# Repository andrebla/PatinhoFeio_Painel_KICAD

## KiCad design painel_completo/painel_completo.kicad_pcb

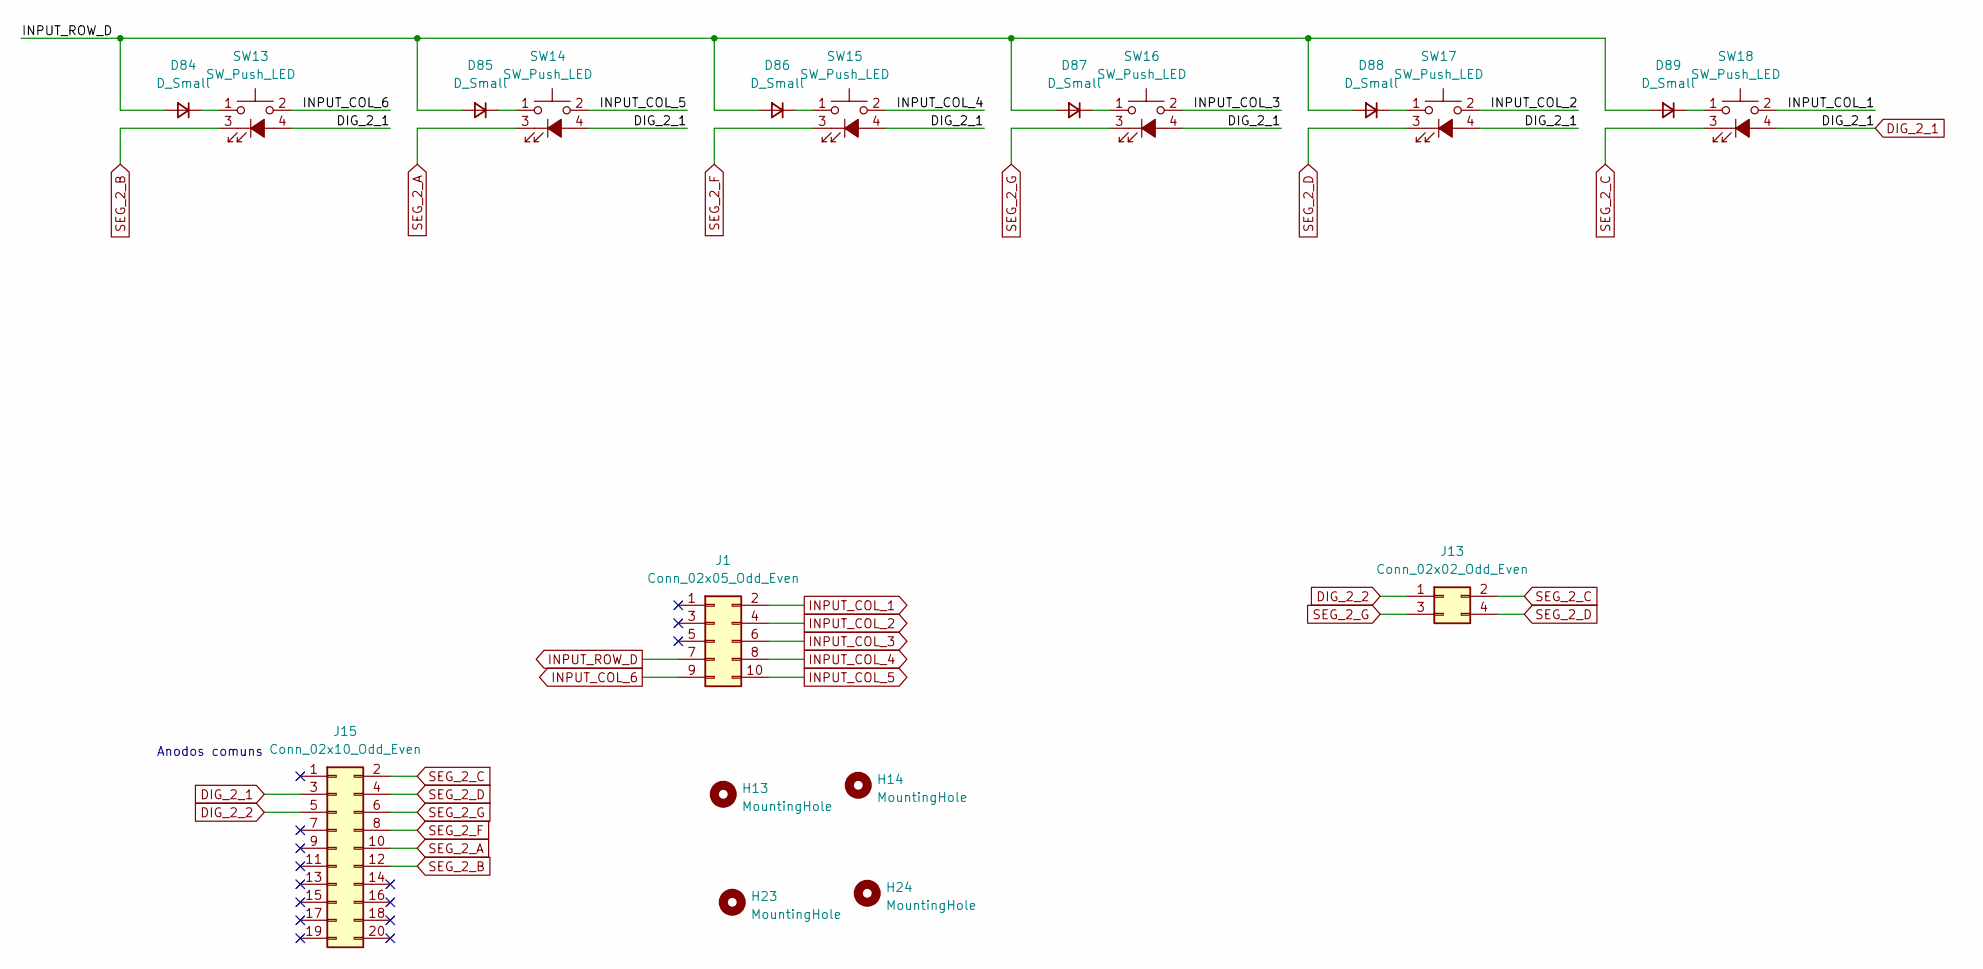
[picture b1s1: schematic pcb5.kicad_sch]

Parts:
D84, D85, D86, D87, D88, D89: D_Small; D_DO-35_SOD27_P7.62mm_Horizontal
H13, H14, H23, H24: MountingHole; MountingHole_3.2mm_M3
J1: Conn_02x05_Odd_Even; PinHeader_2x05_P2.54mm_Vertical
J13: Conn_02x02_Odd_Even; PinHeader_2x02_P2.54mm_Vertical
J15: Conn_02x10_Odd_Even; PinHeader_2x10_P2.54mm_Vertical
SW13, SW14, SW15, SW16, SW17, SW18: SW_Push_LED; R16-503

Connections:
DIG_2_1: J15.3, SW13.4 (A), SW14.4 (A), SW15.4 (A), SW16.4 (A), SW17.4 (A), SW18.4 (A); also elsewhere on the board
DIG_2_2: J13.1, J15.5; also elsewhere on the board
GPIO9: D84.2 (A), D85.2 (A), D86.2 (A), D87.2 (A), D88.2 (A), D89.2 (A), J1.7; also elsewhere on the board
GPIO10: J1.2, SW18.2; also elsewhere on the board
GPIO11: J1.4, SW17.2; also elsewhere on the board
GPIO12: J1.6, SW16.2; also elsewhere on the board
GPIO13: J1.8, SW15.2; also elsewhere on the board
GPIO14: J1.10, SW14.2; also elsewhere on the board
GPIO15: J1.9, SW13.2; also elsewhere on the board
unnamed: D84.1 (K), SW13.1
unnamed: D85.1 (K), SW14.1
unnamed: D86.1 (K), SW15.1
unnamed: D87.1 (K), SW16.1
unnamed: D88.1 (K), SW17.1
unnamed: D89.1 (K), SW18.1
SEG_2_A: J15.10, SW14.3 (K); also elsewhere on the board
SEG_2_B: J15.12, SW13.3 (K); also elsewhere on the board
SEG_2_C: J13.2, J15.2, SW18.3 (K); also elsewhere on the board
SEG_2_D: J13.4, J15.4, SW17.3 (K); also elsewhere on the board
SEG_2_F: J15.8, SW15.3 (K); also elsewhere on the board
SEG_2_G: J13.3, J15.6, SW16.3 (K); also elsewhere on the board

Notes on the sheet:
Anodos comuns

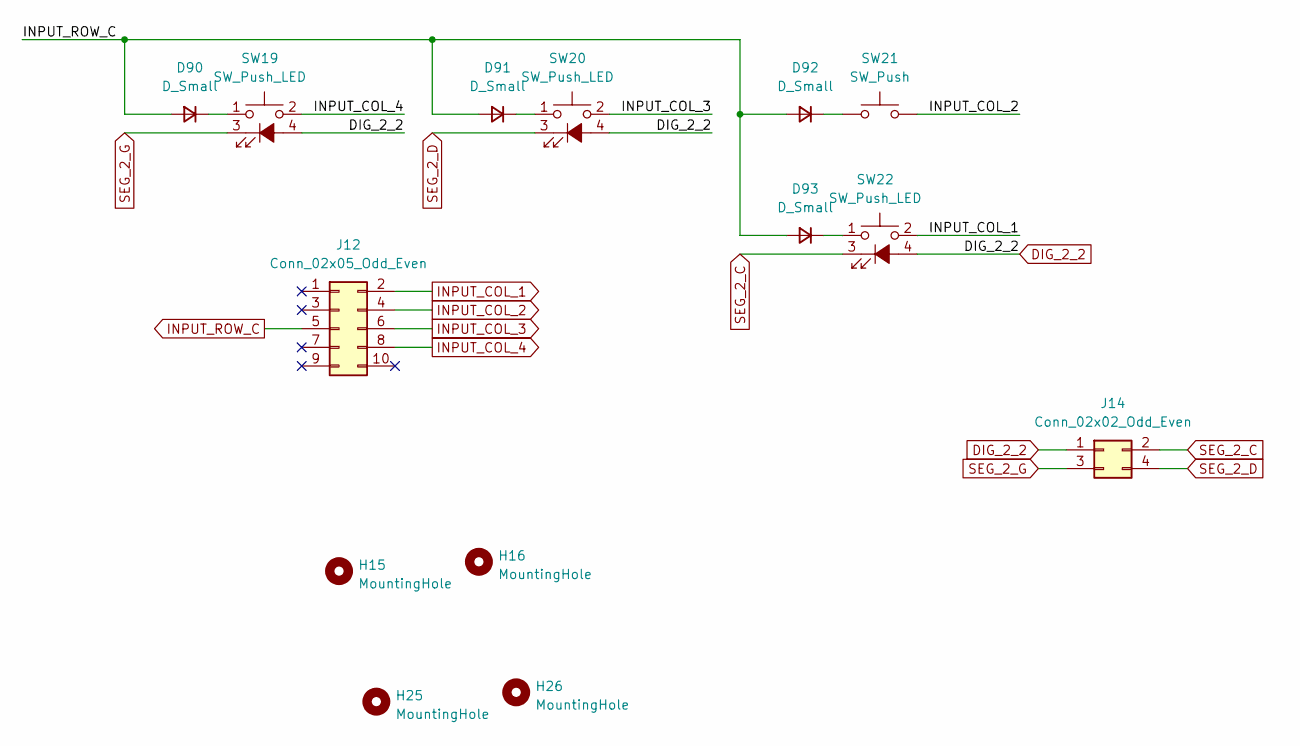
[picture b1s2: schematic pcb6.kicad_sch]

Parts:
D90, D91, D92, D93: D_Small; D_DO-35_SOD27_P7.62mm_Horizontal
H15, H16, H25, H26: MountingHole; MountingHole_3.2mm_M3
J12: Conn_02x05_Odd_Even; PinHeader_2x05_P2.54mm_Vertical
J14: Conn_02x02_Odd_Even; PinHeader_2x02_P2.54mm_Vertical
SW19, SW20, SW22: SW_Push_LED; R16-503
SW21: SW_Push; PinHeader_1x02_P2.54mm_Vertical

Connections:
DIG_2_2: J14.1, SW19.4 (A), SW20.4 (A), SW22.4 (A); also elsewhere on the board
GPIO8: D90.2 (A), D91.2 (A), D92.2 (A), D93.2 (A), J12.5; also elsewhere on the board
GPIO10: J12.2, SW22.2; also elsewhere on the board
GPIO11: J12.4, SW21.2; also elsewhere on the board
GPIO12: J12.6, SW20.2; also elsewhere on the board
GPIO13: J12.8, SW19.2; also elsewhere on the board
unnamed: D90.1 (K), SW19.1
unnamed: D91.1 (K), SW20.1
unnamed: D92.1 (K), SW21.1
unnamed: D93.1 (K), SW22.1
SEG_2_C: J14.2, SW22.3 (K); also elsewhere on the board
SEG_2_D: J14.4, SW20.3 (K); also elsewhere on the board
SEG_2_G: J14.3, SW19.3 (K); also elsewhere on the board

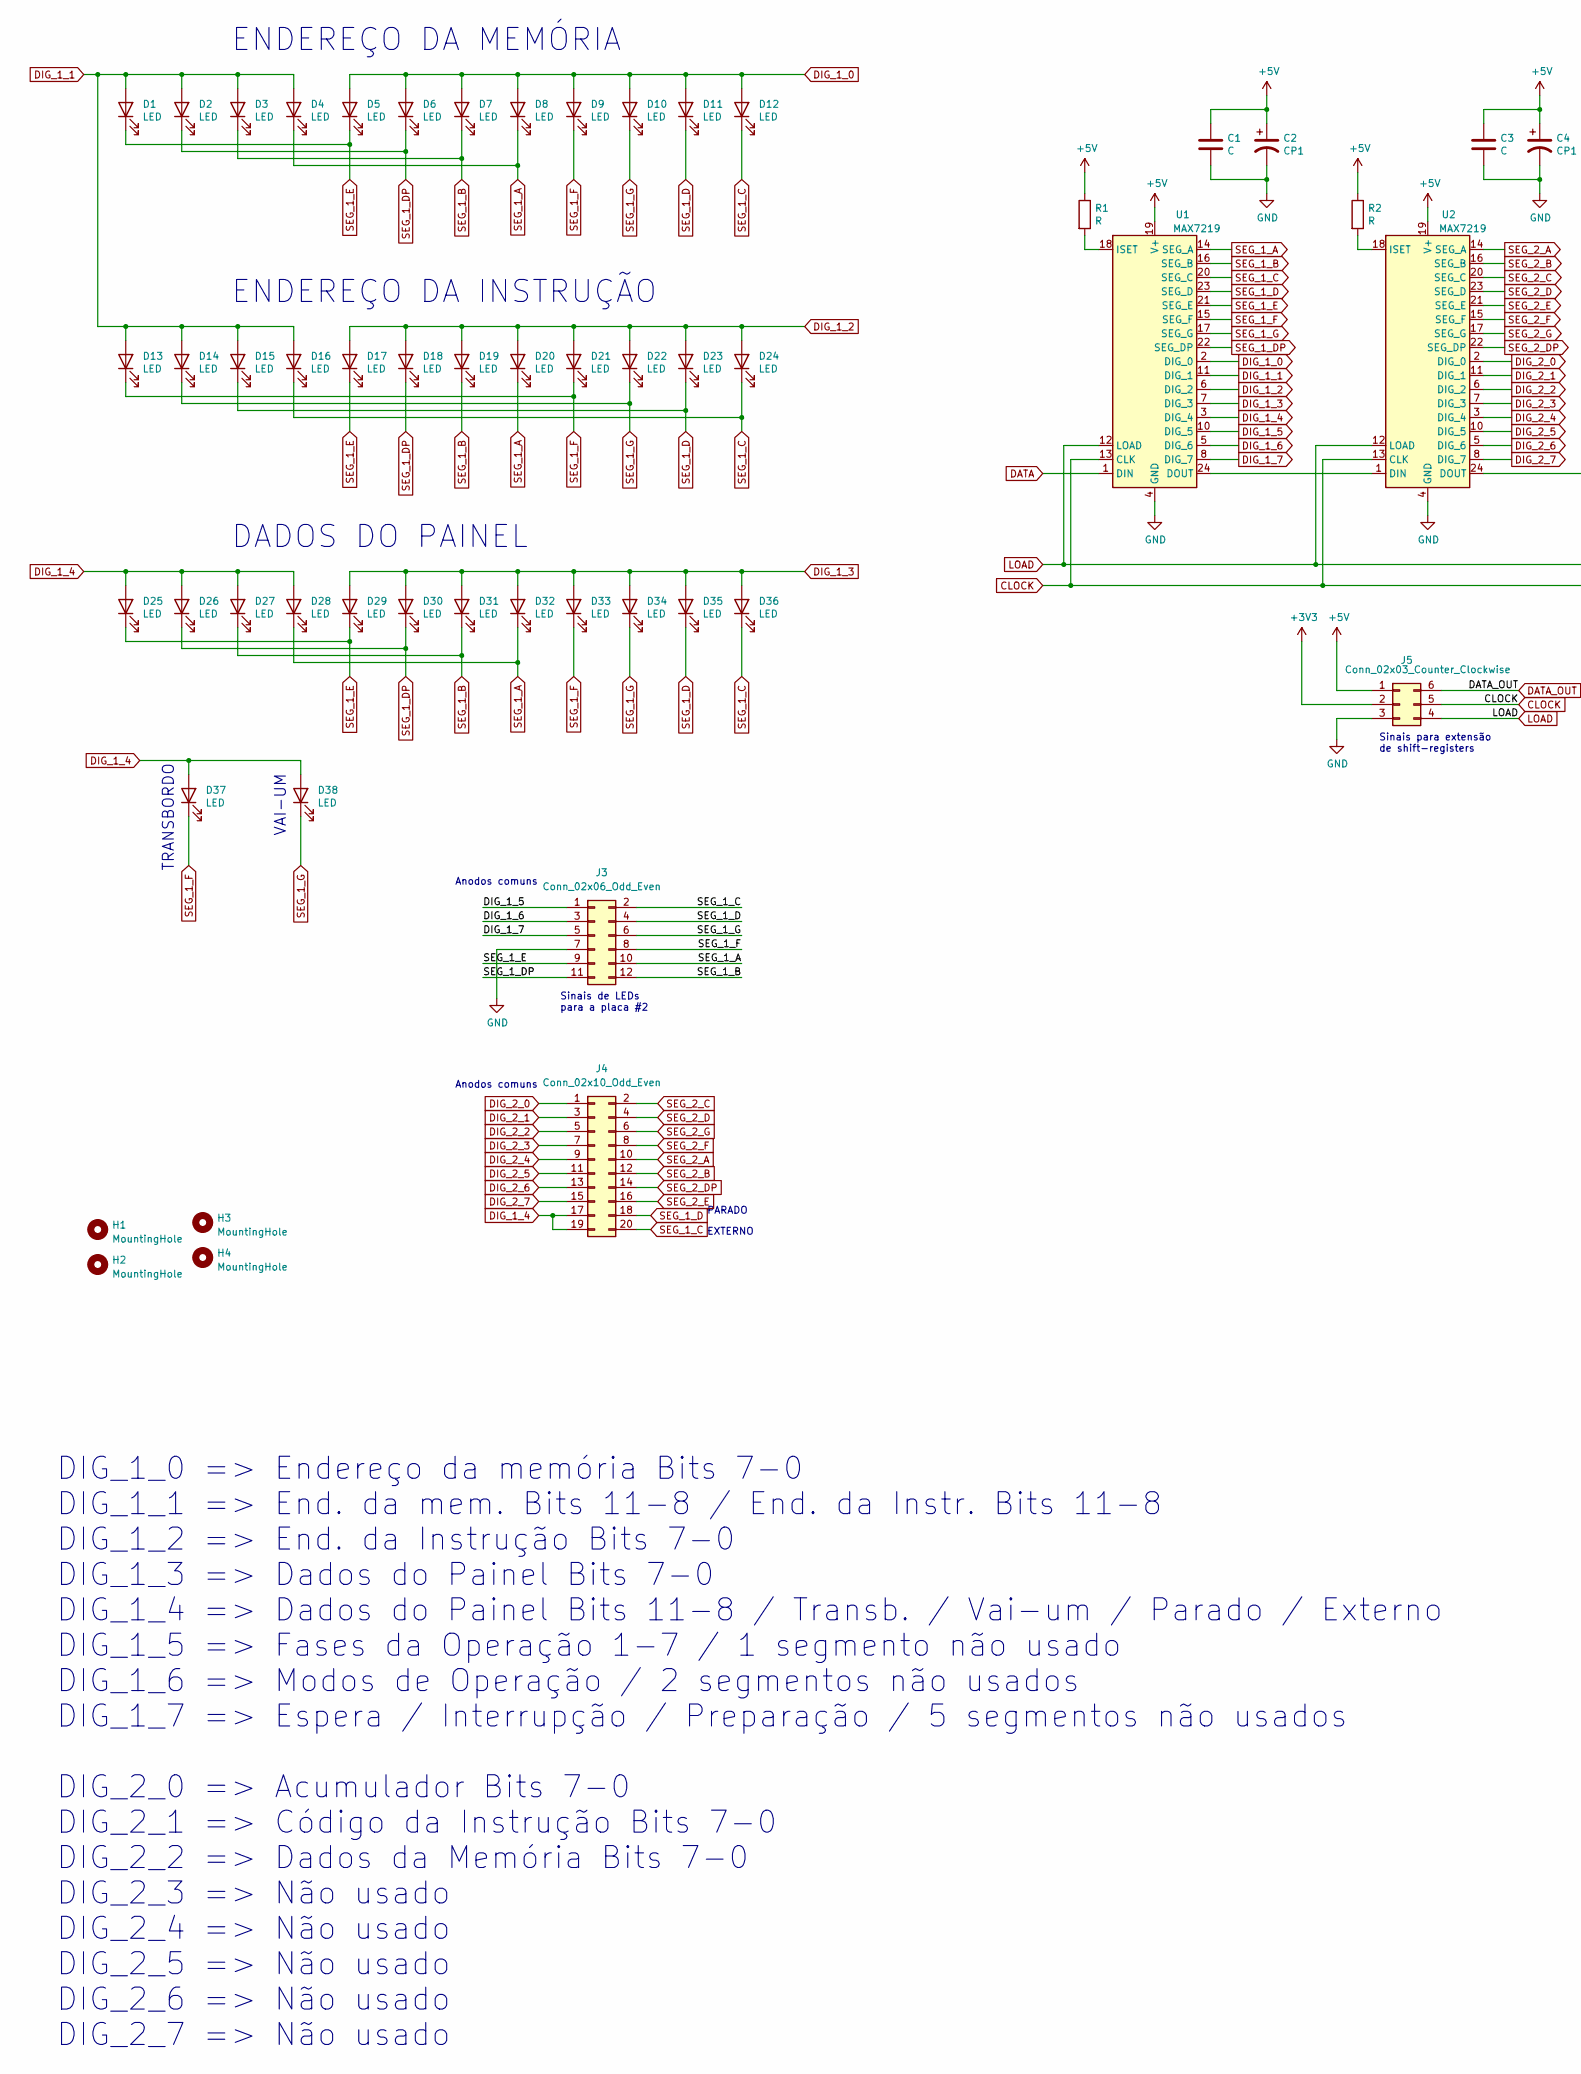
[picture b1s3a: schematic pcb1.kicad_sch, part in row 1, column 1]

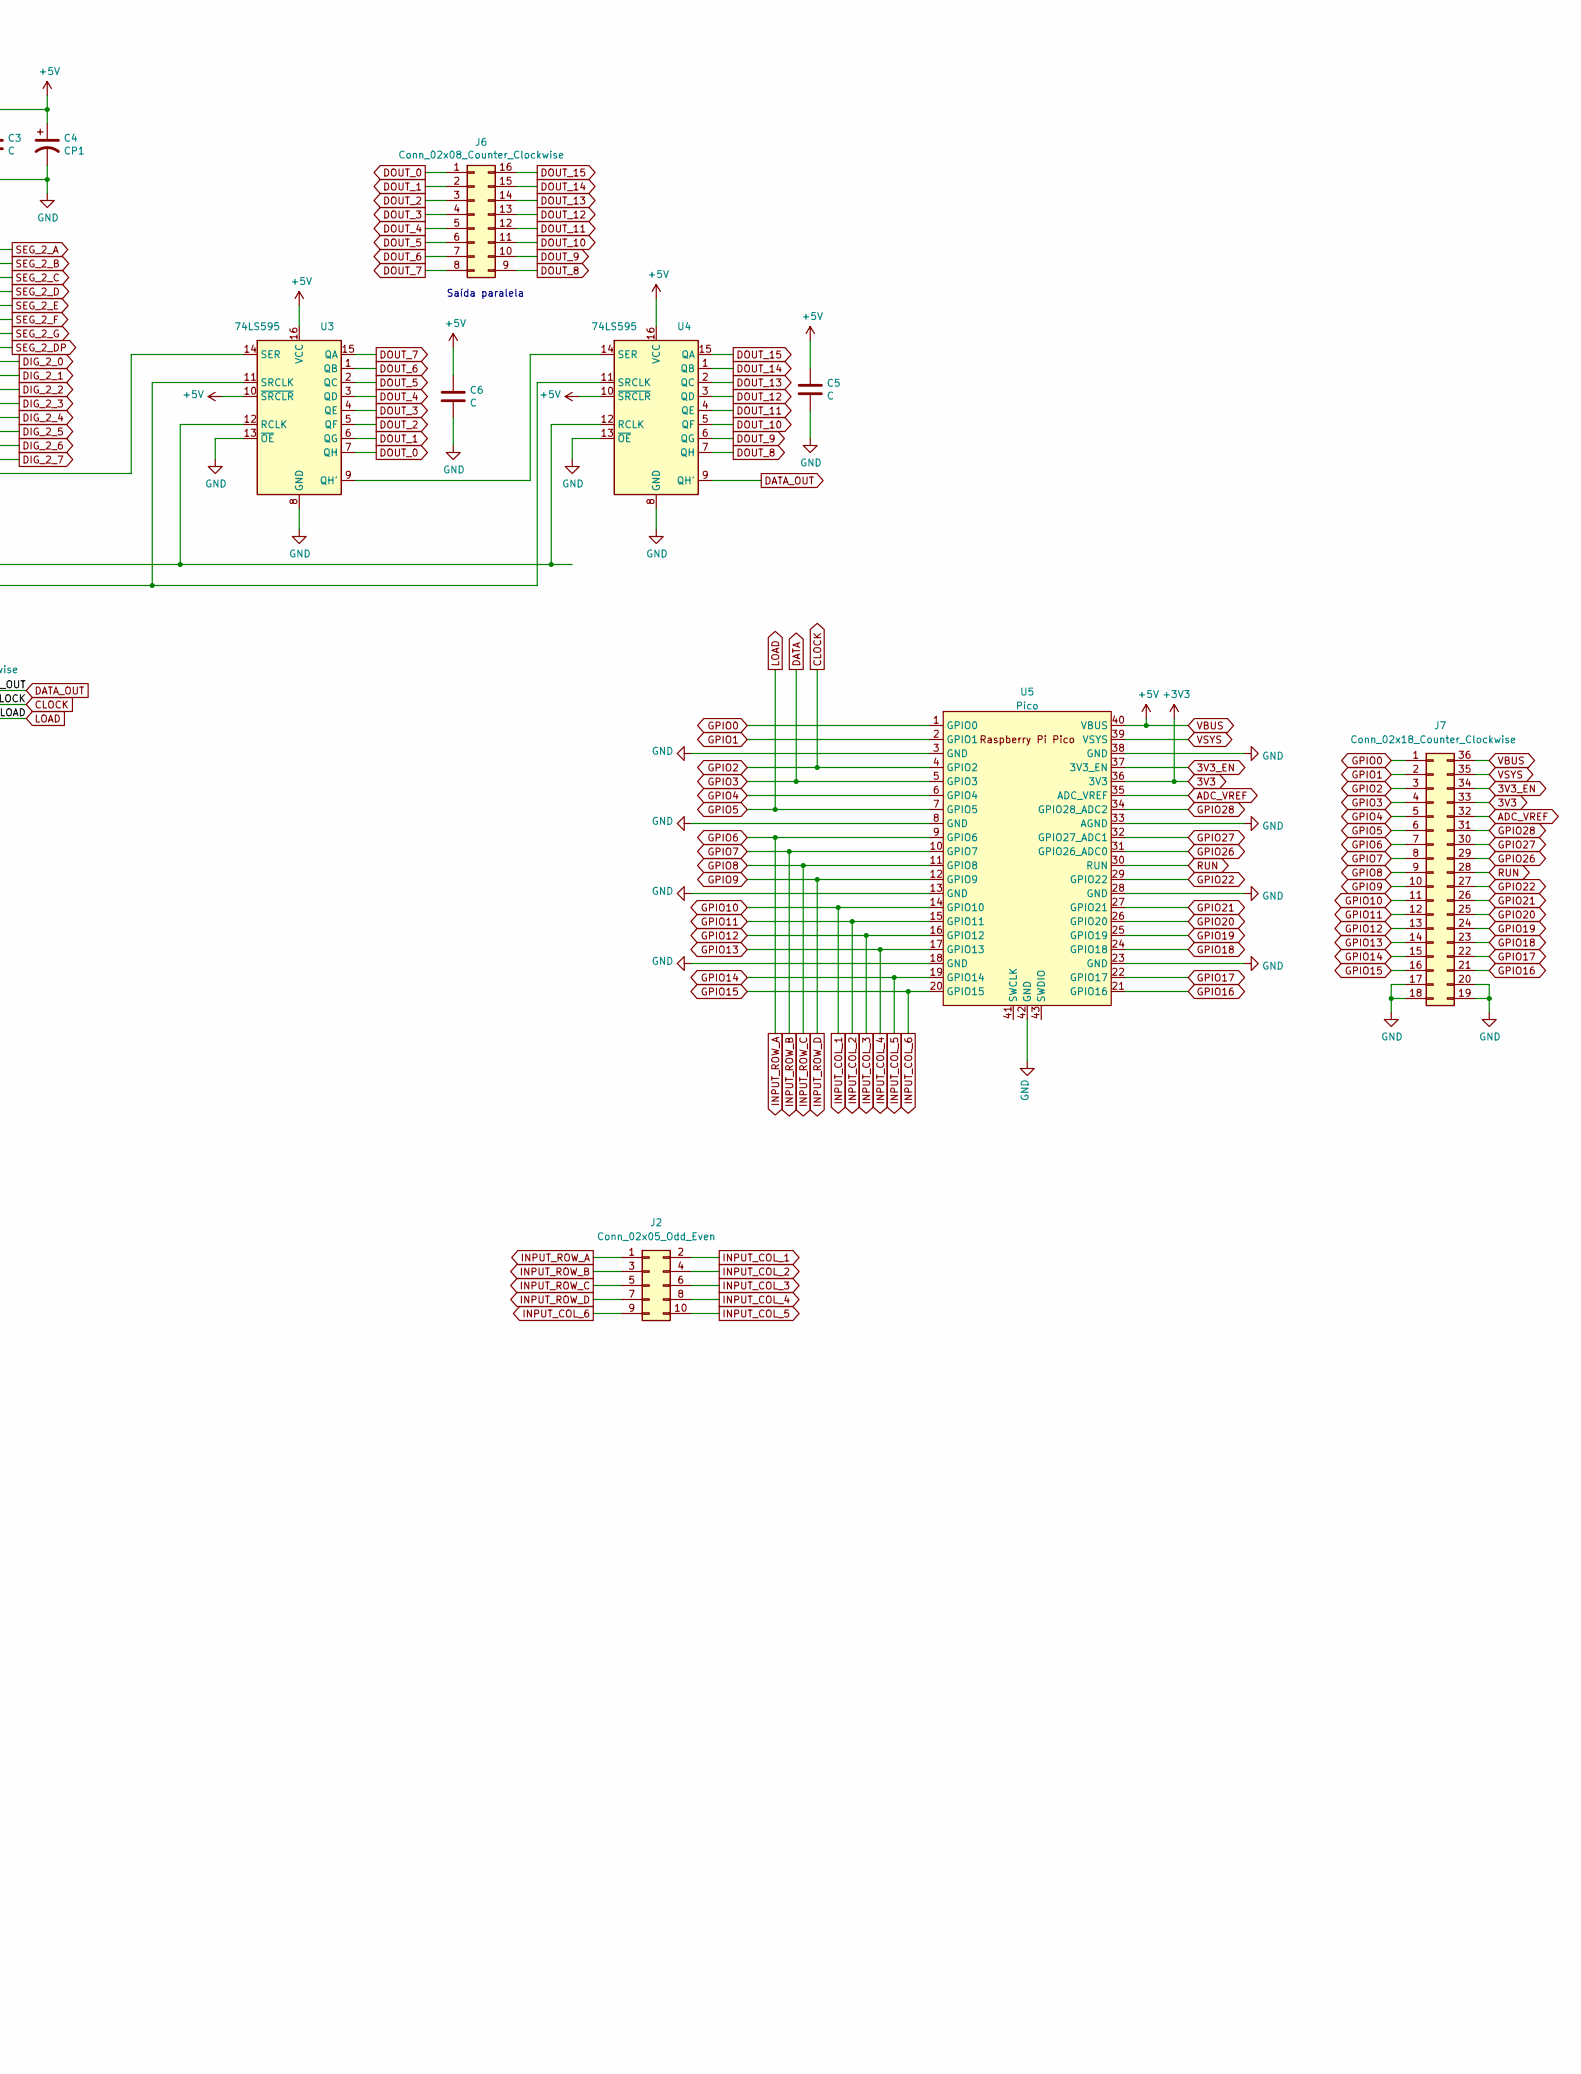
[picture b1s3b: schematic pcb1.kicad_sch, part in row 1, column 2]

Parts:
C1, C3, C5, C6: C; C_Disc_D5.0mm_W2.5mm_P2.50mm
C2, C4: CP1; CP_Radial_D4.0mm_P2.00mm
D1, D2, D3, D4, D5, D6, D7, D8, D9, D10, D11, D12, D13, D14, D15, D16, D17, D18, D19, D20, D21, D22, D23, D24, D25, D26, D27, D28, D29, D30, D31, D32, D33, D34, D35, D36, D37, D38: LED; LED_D3.0mm
H1, H2, H3, H4: MountingHole; MountingHole_3.2mm_M3
J2: Conn_02x05_Odd_Even; PinHeader_2x05_P2.54mm_Vertical
J3: Conn_02x06_Odd_Even; PinHeader_2x06_P2.54mm_Vertical
J4: Conn_02x10_Odd_Even; PinHeader_2x10_P2.54mm_Vertical
J5: Conn_02x03_Counter_Clockwise; PinHeader_2x03_P2.54mm_Vertical
J6: Conn_02x08_Counter_Clockwise; PinHeader_2x08_P2.54mm_Vertical
J7: Conn_02x18_Counter_Clockwise; PinHeader_2x18_P2.54mm_Vertical
R1, R2: R; R_Axial_DIN0207_L6.3mm_D2.5mm_P10.16mm_Horizontal
U1, U2: MAX7219; DIP-24_W7.62mm_Socket_LongPads
U3, U4: 74LS595; DIP-16_W7.62mm_LongPads
U5: Pico; RPi_Pico_SMD_TH

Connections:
3V3: J5.2, J7.33, U5.36 (3V3)
3V3_EN: J7.34, U5.37 (3V3_EN)
ADC_VREF: J7.32, U5.35 (ADC_VREF)
CLOCK: J5.5, J7.3, U1.13 (CLK), U2.13 (CLK), U3.11 (SRCLK), U4.11 (SRCLK), U5.4 (GPIO2)
DATA: J7.4, U1.1 (DIN), U5.5 (GPIO3)
DATA_OUT: J5.6, U4.9 (QH')
DIG_1_0: D5.2 (A), D6.2 (A), D7.2 (A), D8.2 (A), D9.2 (A), D10.2 (A), D11.2 (A), D12.2 (A), U1.2 (DIG_0)
DIG_1_1: D1.2 (A), D2.2 (A), D3.2 (A), D4.2 (A), D13.2 (A), D14.2 (A), D15.2 (A), D16.2 (A), U1.11 (DIG_1)
DIG_1_2: D17.2 (A), D18.2 (A), D19.2 (A), D20.2 (A), D21.2 (A), D22.2 (A), D23.2 (A), D24.2 (A), U1.6 (DIG_2)
DIG_1_3: D29.2 (A), D30.2 (A), D31.2 (A), D32.2 (A), D33.2 (A), D34.2 (A), D35.2 (A), D36.2 (A), U1.7 (DIG_3)
DIG_1_4: D25.2 (A), D26.2 (A), D27.2 (A), D28.2 (A), D37.2 (A), D38.2 (A), J4.17, J4.19, U1.3 (DIG_4); also elsewhere on the board
DIG_1_5: J3.1, U1.10 (DIG_5)
DIG_1_6: J3.3, U1.5 (DIG_6)
DIG_1_7: J3.5, U1.8 (DIG_7)
DIG_2_0: J4.1, U2.2 (DIG_0); also elsewhere on the board
DIG_2_1: J4.3, U2.11 (DIG_1); also elsewhere on the board
DIG_2_2: J4.5, U2.6 (DIG_2); also elsewhere on the board
DIG_2_3: J4.7, U2.7 (DIG_3); also elsewhere on the board
DIG_2_4: J4.9, U2.3 (DIG_4); also elsewhere on the board
DIG_2_5: J4.11, U2.10 (DIG_5); also elsewhere on the board
DIG_2_6: J4.13, U2.5 (DIG_6); also elsewhere on the board
DIG_2_7: J4.15, U2.8 (DIG_7); also elsewhere on the board
DOUT_0: J6.1, U3.7 (QH)
DOUT_1: J6.2, U3.6 (QG)
DOUT_2: J6.3, U3.5 (QF)
DOUT_3: J6.4, U3.4 (QE)
DOUT_4: J6.5, U3.3 (QD)
DOUT_5: J6.6, U3.2 (QC)
DOUT_6: J6.7, U3.1 (QB)
DOUT_7: J6.8, U3.15 (QA)
DOUT_8: J6.9, U4.7 (QH)
DOUT_9: J6.10, U4.6 (QG)
DOUT_10: J6.11, U4.5 (QF)
DOUT_11: J6.12, U4.4 (QE)
DOUT_12: J6.13, U4.3 (QD)
DOUT_13: J6.14, U4.2 (QC)
DOUT_14: J6.15, U4.1 (QB)
DOUT_15: J6.16, U4.15 (QA)
GND: C1.2, C2.2, C3.2, C4.2, C5.2, C6.2, J3.7, J5.3, J7.17, J7.18, J7.19, J7.20, U1.4 (GND), U1.9 (GND), U2.4 (GND), U2.9 (GND), U3.8 (GND), U3.13 (~OE), U4.8 (GND), U4.13 (~OE), U5.3 (GND), U5.8 (GND), U5.13 (GND), U5.18 (GND), U5.23 (GND), U5.28 (GND), U5.33 (AGND), U5.38 (GND), U5.42 (GND); also elsewhere on the board
GPIO0: J7.1, U5.1 (GPIO0)
GPIO1: J7.2, U5.2 (GPIO1)
GPIO4: J7.5, U5.6 (GPIO4)
GPIO5: J5.4, J7.6, U1.12 (LOAD), U2.12 (LOAD), U3.12 (RCLK), U4.12 (RCLK), U5.7 (GPIO5)
GPIO6: J2.1, J7.7, U5.9 (GPIO6); also elsewhere on the board
GPIO7: J2.3, J7.8, U5.10 (GPIO7); also elsewhere on the board
GPIO8: J2.5, J7.9, U5.11 (GPIO8); also elsewhere on the board
GPIO9: J2.7, J7.10, U5.12 (GPIO9); also elsewhere on the board
GPIO10: J2.2, J7.11, U5.14 (GPIO10); also elsewhere on the board
GPIO11: J2.4, J7.12, U5.15 (GPIO11); also elsewhere on the board
GPIO12: J2.6, J7.13, U5.16 (GPIO12); also elsewhere on the board
GPIO13: J2.8, J7.14, U5.17 (GPIO13); also elsewhere on the board
GPIO14: J2.10, J7.15, U5.19 (GPIO14); also elsewhere on the board
GPIO15: J2.9, J7.16, U5.20 (GPIO15); also elsewhere on the board
GPIO16: J7.21, U5.21 (GPIO16)
GPIO17: J7.22, U5.22 (GPIO17)
GPIO18: J7.23, U5.24 (GPIO18)
GPIO19: J7.24, U5.25 (GPIO19)
GPIO20: J7.25, U5.26 (GPIO20)
GPIO21: J7.26, U5.27 (GPIO21)
GPIO22: J7.27, U5.29 (GPIO22)
GPIO26: J7.29, U5.31 (GPIO26_ADC0)
GPIO27: J7.30, U5.32 (GPIO27_ADC1)
GPIO28: J7.31, U5.34 (GPIO28_ADC2)
unnamed: R1.2, U1.18 (ISET)
unnamed: R2.2, U2.18 (ISET)
unnamed: U1.24 (DOUT), U2.1 (DIN)
unnamed: U2.24 (DOUT), U3.14 (SER)
unnamed: U3.9 (QH'), U4.14 (SER)
RUN: J7.28, U5.30 (RUN)
SEG_1_A: D4.1 (K), D8.1 (K), D20.1 (K), D28.1 (K), D32.1 (K), J3.10, U1.14 (SEG_A)
SEG_1_B: D3.1 (K), D7.1 (K), D19.1 (K), D27.1 (K), D31.1 (K), J3.12, U1.16 (SEG_B)
SEG_1_C: D12.1 (K), D16.1 (K), D24.1 (K), D36.1 (K), J3.2, J4.20, U1.20 (SEG_C); also elsewhere on the board
SEG_1_D: D11.1 (K), D15.1 (K), D23.1 (K), D35.1 (K), J3.4, J4.18, U1.23 (SEG_D); also elsewhere on the board
SEG_1_DP: D2.1 (K), D6.1 (K), D18.1 (K), D26.1 (K), D30.1 (K), J3.11, U1.22 (SEG_DP)
SEG_1_E: D1.1 (K), D5.1 (K), D17.1 (K), D25.1 (K), D29.1 (K), J3.9, U1.21 (SEG_E)
SEG_1_F: D9.1 (K), D13.1 (K), D21.1 (K), D33.1 (K), D37.1 (K), J3.8, U1.15 (SEG_F)
SEG_1_G: D10.1 (K), D14.1 (K), D22.1 (K), D34.1 (K), D38.1 (K), J3.6, U1.17 (SEG_G)
SEG_2_A: J4.10, U2.14 (SEG_A); also elsewhere on the board
SEG_2_B: J4.12, U2.16 (SEG_B); also elsewhere on the board
SEG_2_C: J4.2, U2.20 (SEG_C); also elsewhere on the board
SEG_2_D: J4.4, U2.23 (SEG_D); also elsewhere on the board
SEG_2_DP: J4.14, U2.22 (SEG_DP); also elsewhere on the board
SEG_2_E: J4.16, U2.21 (SEG_E); also elsewhere on the board
SEG_2_F: J4.8, U2.15 (SEG_F); also elsewhere on the board
SEG_2_G: J4.6, U2.17 (SEG_G); also elsewhere on the board
VBUS: C1.1, C2.1, C3.1, C4.1, C5.1, C6.1, J5.1, J7.36, R1.1, R2.1, U1.19 (V+), U2.19 (V+), U3.10 (~SRCLR), U3.16 (VCC), U4.10 (~SRCLR), U4.16 (VCC), U5.40 (VBUS)
VSYS: J7.35, U5.39 (VSYS)

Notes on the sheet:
VAI-UM
ENDEREÇO DA INSTRUÇÃO
EXTERNO
PARADO
Sinais para extensão de shift-registers
Sinais de LEDs para a placa #2
Saída paralela
Anodos comuns
DADOS DO PAINEL
ENDEREÇO DA MEMÓRIA
TRANSBORDO
DIG_1_0 => Endereço da memória Bits 7-0 DIG_1_1 => End. da mem. Bits 11-8 / End. da Instr. Bits 11-8 DIG_1_2 => End. da Instrução Bits 7-0 DIG_1_3 => Dados do Painel Bits 7-0 DIG_1_4 => Dados do Painel Bits 11-8 / Transb. / Vai-um / Parado / Externo DIG_1_5 => Fases da Operação 1-7 / 1 segmento não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

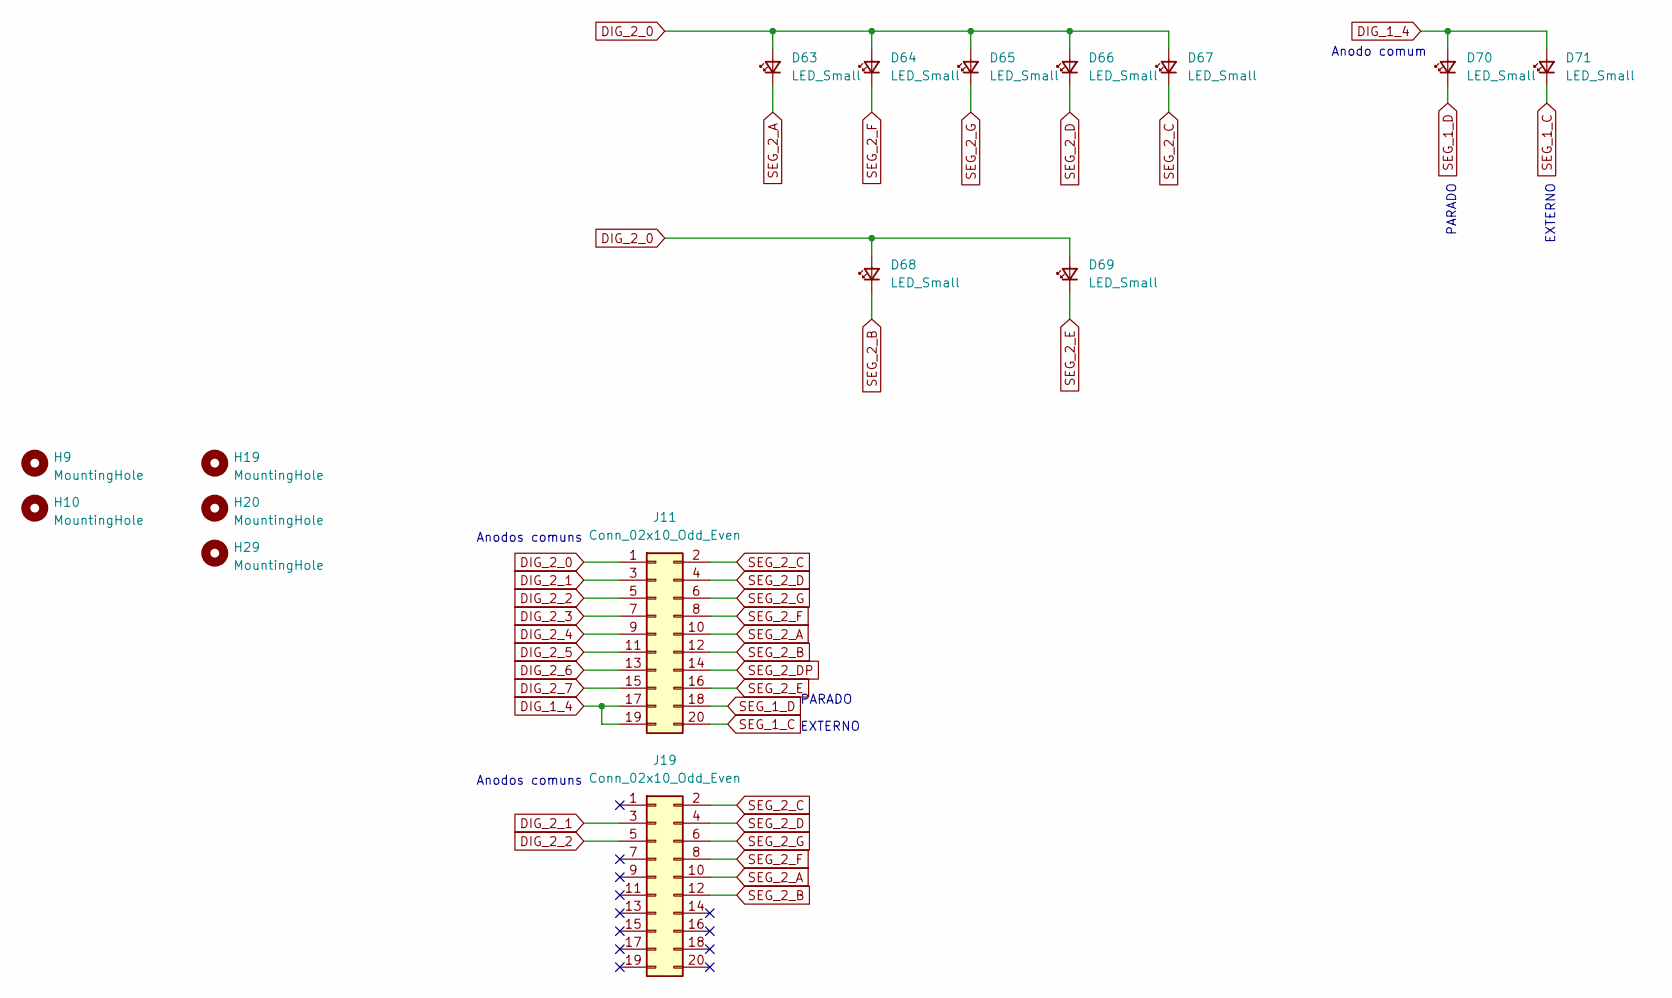
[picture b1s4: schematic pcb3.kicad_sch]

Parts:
D63, D64, D65, D66, D67, D68, D69, D70, D71: LED_Small; LED_D5.0mm
H9, H10, H19, H20, H29: MountingHole; MountingHole_3.2mm_M3
J11, J19: Conn_02x10_Odd_Even; PinHeader_2x10_P2.54mm_Vertical

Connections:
DIG_1_4: D70.2 (A), D71.2 (A), J11.17, J11.19; also elsewhere on the board
DIG_2_0: D63.2 (A), D64.2 (A), D65.2 (A), D66.2 (A), D67.2 (A), D68.2 (A), D69.2 (A), J11.1; also elsewhere on the board
DIG_2_1: J11.3, J19.3; also elsewhere on the board
DIG_2_2: J11.5, J19.5; also elsewhere on the board
DIG_2_3: J11.7; also elsewhere on the board
DIG_2_4: J11.9; also elsewhere on the board
DIG_2_5: J11.11; also elsewhere on the board
DIG_2_6: J11.13; also elsewhere on the board
DIG_2_7: J11.15; also elsewhere on the board
SEG_1_C: D71.1 (K), J11.20; also elsewhere on the board
SEG_1_D: D70.1 (K), J11.18; also elsewhere on the board
SEG_2_A: D63.1 (K), J11.10, J19.10; also elsewhere on the board
SEG_2_B: D68.1 (K), J11.12, J19.12; also elsewhere on the board
SEG_2_C: D67.1 (K), J11.2, J19.2; also elsewhere on the board
SEG_2_D: D66.1 (K), J11.4, J19.4; also elsewhere on the board
SEG_2_DP: J11.14; also elsewhere on the board
SEG_2_E: D69.1 (K), J11.16; also elsewhere on the board
SEG_2_F: D64.1 (K), J11.8, J19.8; also elsewhere on the board
SEG_2_G: D65.1 (K), J11.6, J19.6; also elsewhere on the board

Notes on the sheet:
EXTERNO
PARADO
Anodo comum
Anodos comuns

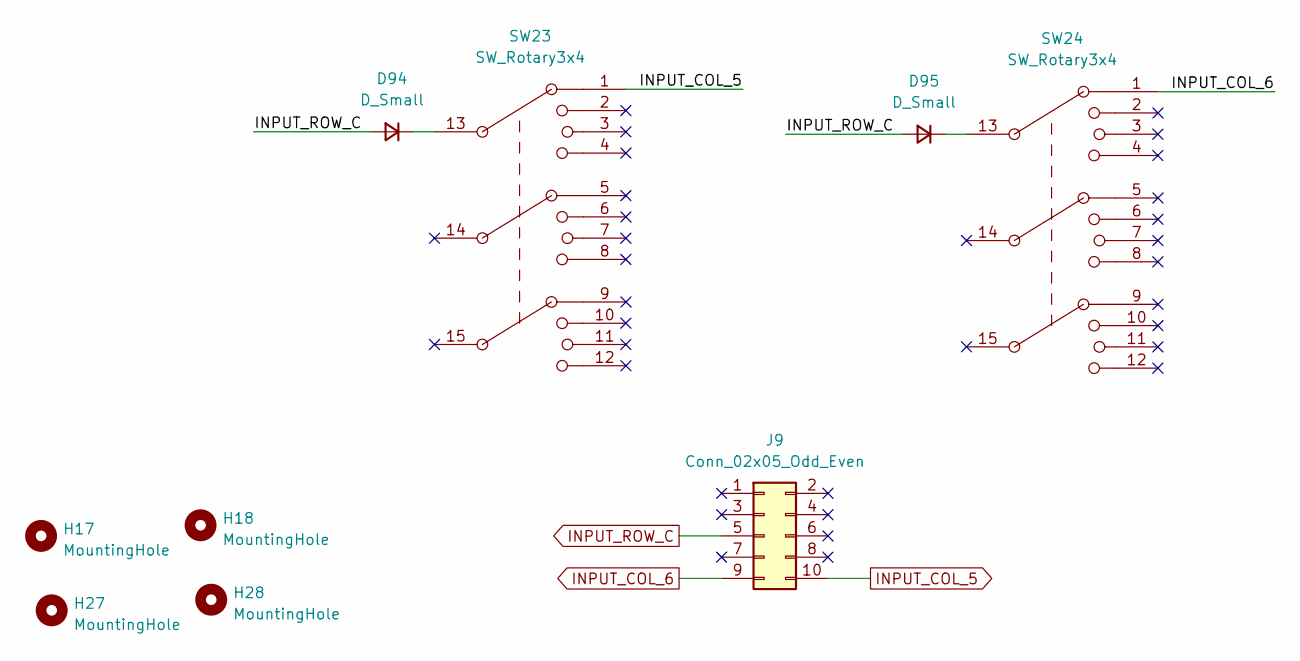
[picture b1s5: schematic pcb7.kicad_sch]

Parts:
D94, D95: D_Small; D_DO-35_SOD27_P7.62mm_Horizontal
H17, H18, H27, H28: MountingHole; MountingHole_3.2mm_M3
J9: Conn_02x05_Odd_Even; PinHeader_2x05_P2.54mm_Vertical
SW23, SW24: SW_Rotary3x4; RTS-01-304-12.7RP

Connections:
GPIO8: D94.2 (A), D95.2 (A), J9.5; also elsewhere on the board
GPIO14: J9.10, SW23.1; also elsewhere on the board
GPIO15: J9.9, SW24.1; also elsewhere on the board
unnamed: D94.1 (K), SW23.13
unnamed: D95.1 (K), SW24.13

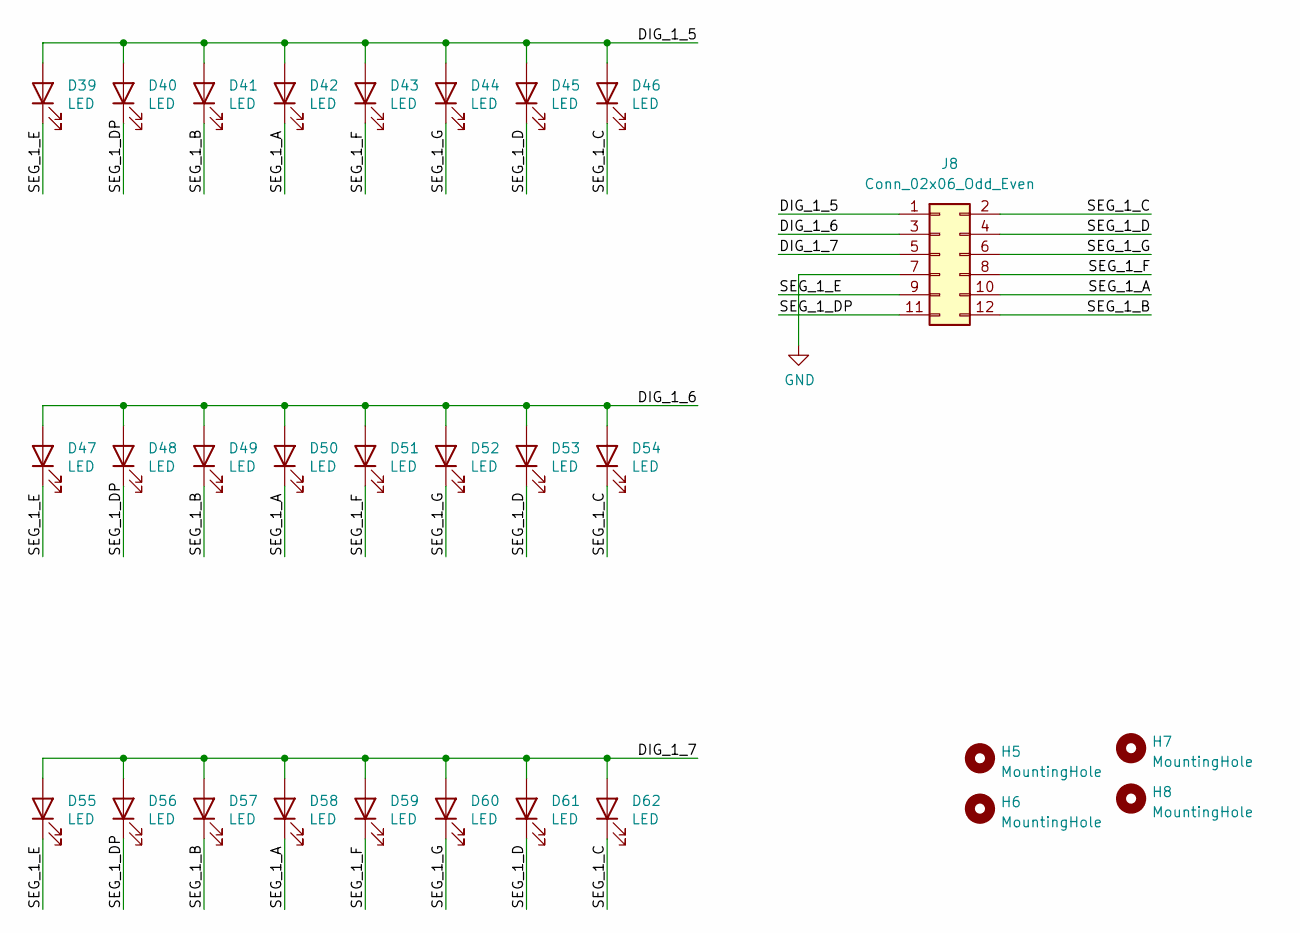
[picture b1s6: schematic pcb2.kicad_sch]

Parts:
D39, D40, D41, D42, D43, D44, D45, D46, D47, D48, D49, D50, D51, D52, D53, D54, D55, D56, D57, D58, D59, D60, D61, D62: LED; LED_D3.0mm
H5, H6, H7, H8: MountingHole; MountingHole_3.2mm_M3
J8: Conn_02x06_Odd_Even; PinHeader_2x06_P2.54mm_Vertical

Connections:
/PCB2/DIG_1_5: D39.2 (A), D40.2 (A), D41.2 (A), D42.2 (A), D43.2 (A), D44.2 (A), D45.2 (A), D46.2 (A), J8.1
/PCB2/DIG_1_6: D47.2 (A), D48.2 (A), D49.2 (A), D50.2 (A), D51.2 (A), D52.2 (A), D53.2 (A), D54.2 (A), J8.3
/PCB2/DIG_1_7: D55.2 (A), D56.2 (A), D57.2 (A), D58.2 (A), D59.2 (A), D60.2 (A), D61.2 (A), D62.2 (A), J8.5
/PCB2/SEG_1_A: D42.1 (K), D50.1 (K), D58.1 (K), J8.10
/PCB2/SEG_1_B: D41.1 (K), D49.1 (K), D57.1 (K), J8.12
/PCB2/SEG_1_C: D46.1 (K), D54.1 (K), D62.1 (K), J8.2
/PCB2/SEG_1_D: D45.1 (K), D53.1 (K), D61.1 (K), J8.4
/PCB2/SEG_1_DP: D40.1 (K), D48.1 (K), D56.1 (K), J8.11
/PCB2/SEG_1_E: D39.1 (K), D47.1 (K), D55.1 (K), J8.9
/PCB2/SEG_1_F: D43.1 (K), D51.1 (K), D59.1 (K), J8.8
/PCB2/SEG_1_G: D44.1 (K), D52.1 (K), D60.1 (K), J8.6
GND: J8.7; also elsewhere on the board

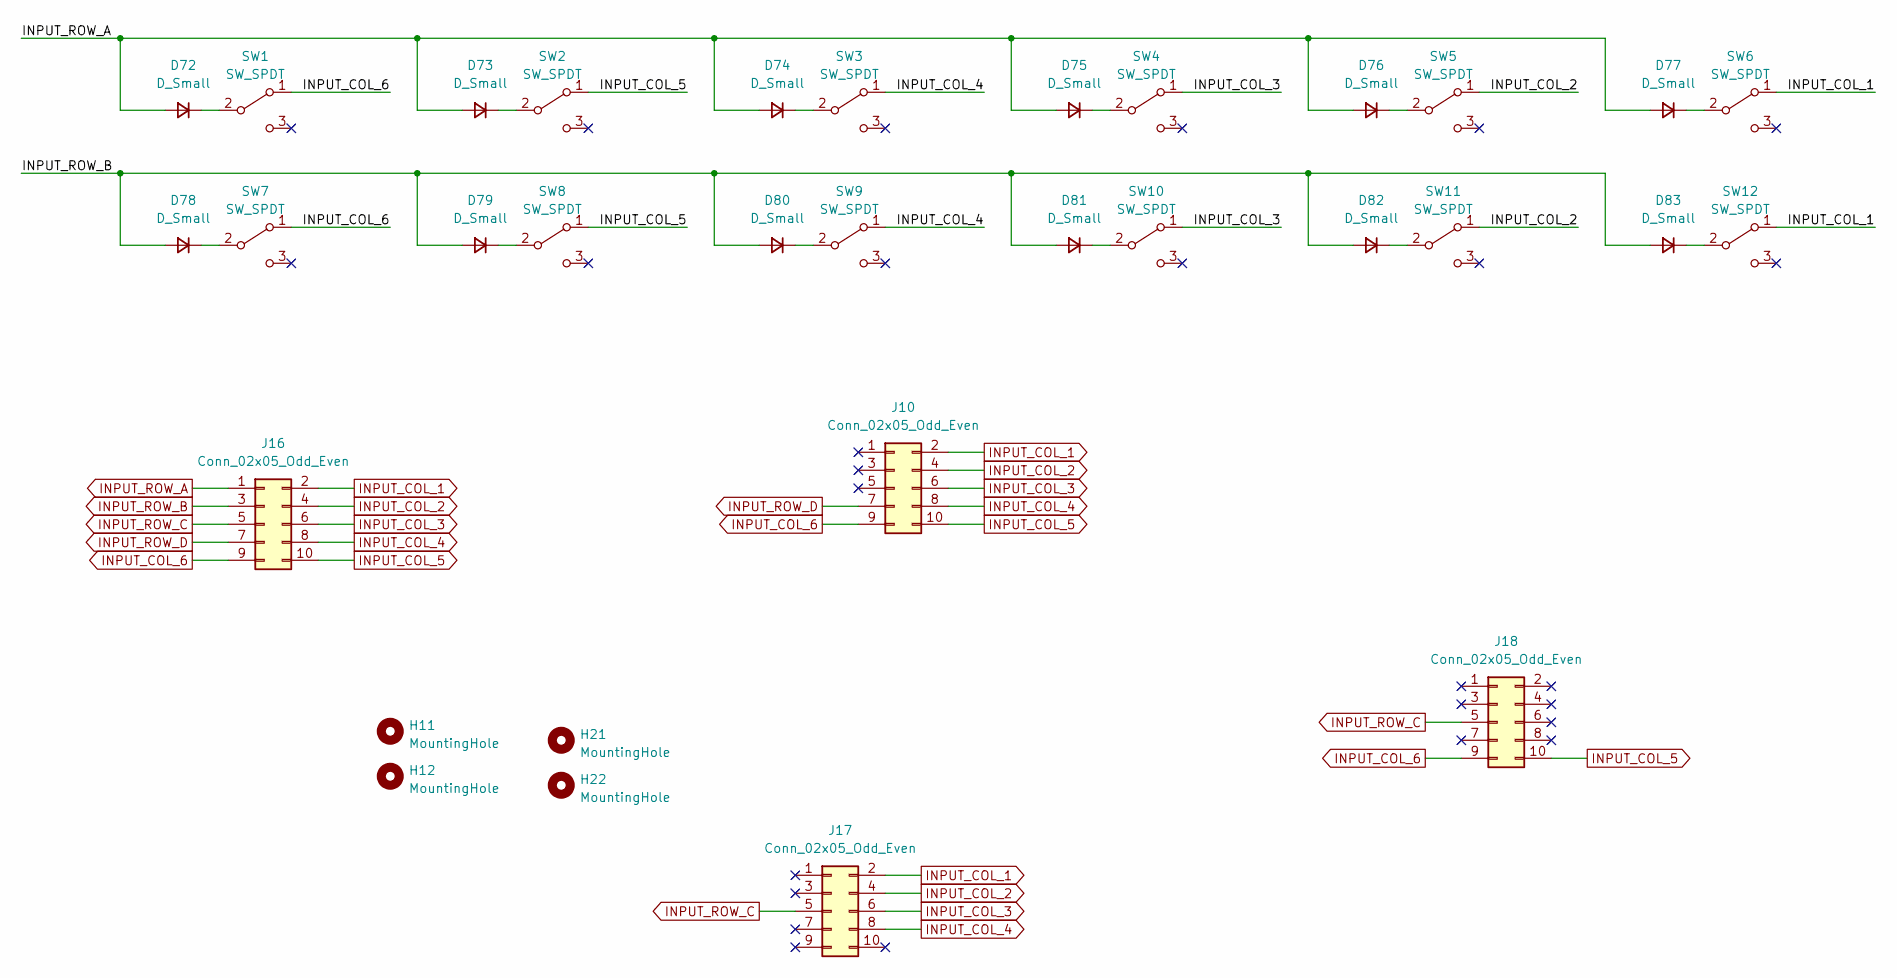
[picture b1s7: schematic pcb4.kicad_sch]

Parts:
D72, D73, D74, D75, D76, D77, D78, D79, D80, D81, D82, D83: D_Small; D_DO-35_SOD27_P7.62mm_Horizontal
H11, H12, H21, H22: MountingHole; MountingHole_3.2mm_M3
J10, J16, J17, J18: Conn_02x05_Odd_Even; PinHeader_2x05_P2.54mm_Vertical
SW1, SW2, SW3, SW4, SW5, SW6, SW7, SW8, SW9, SW10, SW11, SW12: SW_SPDT; MTS-123

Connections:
GPIO6: D72.2 (A), D73.2 (A), D74.2 (A), D75.2 (A), D76.2 (A), D77.2 (A), J16.1; also elsewhere on the board
GPIO7: D78.2 (A), D79.2 (A), D80.2 (A), D81.2 (A), D82.2 (A), D83.2 (A), J16.3; also elsewhere on the board
GPIO8: J16.5, J17.5, J18.5; also elsewhere on the board
GPIO9: J10.7, J16.7; also elsewhere on the board
GPIO10: J10.2, J16.2, J17.2, SW6.1 (A), SW12.1 (A); also elsewhere on the board
GPIO11: J10.4, J16.4, J17.4, SW5.1 (A), SW11.1 (A); also elsewhere on the board
GPIO12: J10.6, J16.6, J17.6, SW4.1 (A), SW10.1 (A); also elsewhere on the board
GPIO13: J10.8, J16.8, J17.8, SW3.1 (A), SW9.1 (A); also elsewhere on the board
GPIO14: J10.10, J16.10, J18.10, SW2.1 (A), SW8.1 (A); also elsewhere on the board
GPIO15: J10.9, J16.9, J18.9, SW1.1 (A), SW7.1 (A); also elsewhere on the board
unnamed: D72.1 (K), SW1.2 (B)
unnamed: D73.1 (K), SW2.2 (B)
unnamed: D74.1 (K), SW3.2 (B)
unnamed: D75.1 (K), SW4.2 (B)
unnamed: D76.1 (K), SW5.2 (B)
unnamed: D77.1 (K), SW6.2 (B)
unnamed: D78.1 (K), SW7.2 (B)
unnamed: D79.1 (K), SW8.2 (B)
unnamed: D80.1 (K), SW9.2 (B)
unnamed: D81.1 (K), SW10.2 (B)
unnamed: D82.1 (K), SW11.2 (B)
unnamed: D83.1 (K), SW12.2 (B)

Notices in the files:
painel_completo/painel_completo.kicad_pcb:
Licensed under CERN-OHL-S v2 or later
https://cern.ch/cern-ohl
